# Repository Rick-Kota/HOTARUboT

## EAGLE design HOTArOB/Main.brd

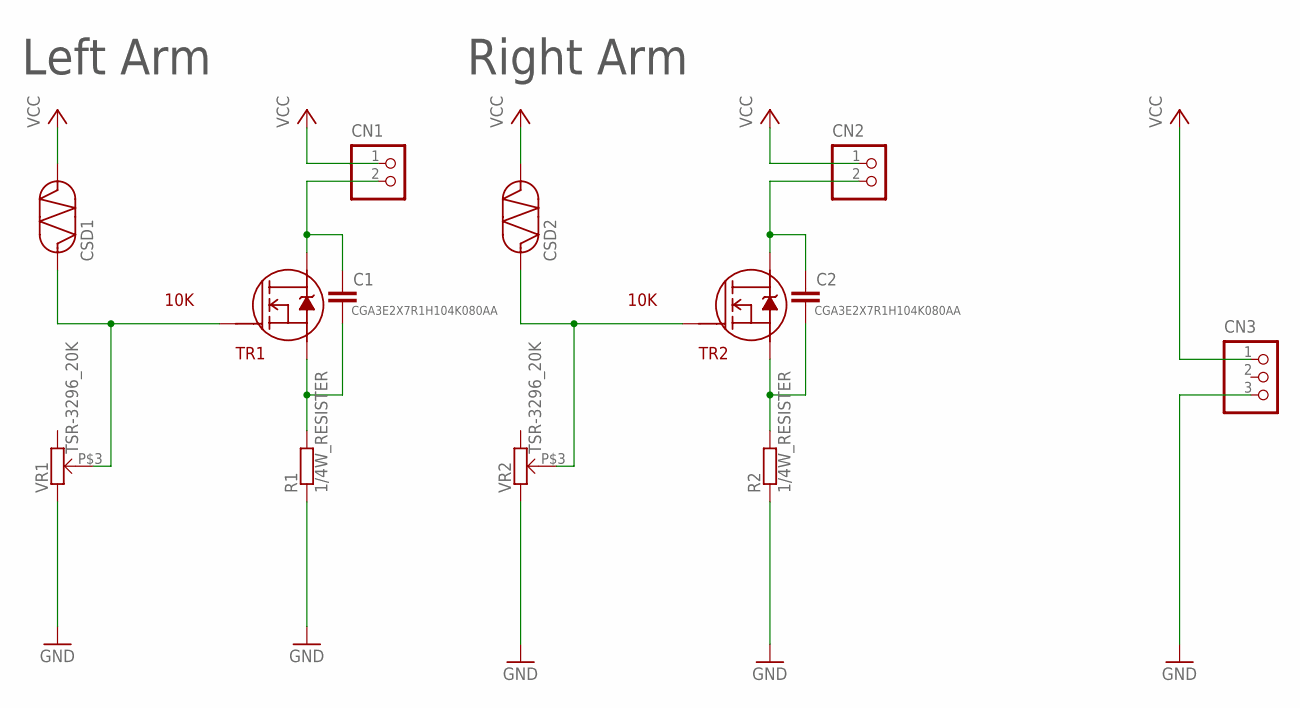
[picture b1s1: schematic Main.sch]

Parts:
C1, C2: CGA3E2X7R1H104K080AA; 0603
CN1, CN2: B2B-XH-A
CN3: B3B-XH-A
CSD1, CSD2: GL5528
R1, R2: 1/4W_RESISTER; MF1/4
TR1, TR2: RN5006; SC-62
VR1, VR2: TSR-3296_20K; TSR-3296

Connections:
GND: CN3.3, R1.P$2 (2), R2.P$2 (2), VR1.P$2 (2), VR2.P$2 (2)
unnamed: C1.P$1 (1), CN1.2, TR1.E (D)
unnamed: C1.P$2 (2), R1.P$1 (1), TR1.C1 (S), TR1.C2 (S)
unnamed: C2.P$1 (1), CN2.2, TR2.E (D)
unnamed: C2.P$2 (2), R2.P$1 (1), TR2.C1 (S), TR2.C2 (S)
unnamed: CSD2.P$1, TR2.B (G), VR2.P$3
unnamed: CSD1.P$1, TR1.B (G), VR1.P$3
VCC: CN1.1, CN2.1, CN3.1, CSD1.P$2, CSD2.P$2

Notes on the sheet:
Left Arm
Right Arm
10K

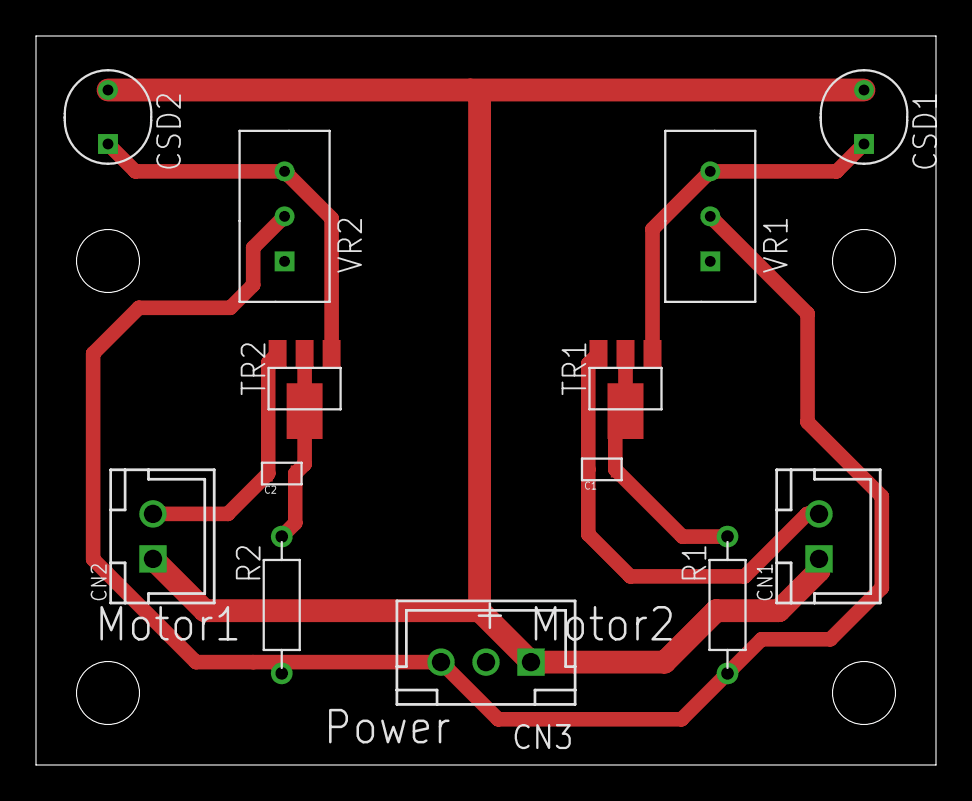
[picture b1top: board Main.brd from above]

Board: 2 copper layers, 50.0 x 40.5 mm, 13 parts (0 on the bottom side), 8 nets.

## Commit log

2018-08-19 build Ver 1.0
    Implement basic functions
2018-08-19 PDF ver.1
2018-09-10 Change sensor
    Photo diode to CdS
2018-10-01 working commit
